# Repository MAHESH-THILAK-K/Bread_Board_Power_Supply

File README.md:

# Bread Board Power Supply

**Board Render**

A compact and easy-to-use breadboard power supply PCB designed to deliver stable, regulated DC power for electronics prototyping. This board plugs directly into standard solderless breadboards and provides clean **5V and/or 3.3V outputs**, making it ideal for students, hobbyists, and embedded system developers.

The design focuses on simplicity, reliability, and beginner-friendly usage for powering microcontrollers, sensors, and logic circuits during development and testing.

---

## 📌 Key Features

### Power Regulation

* Regulated **5V and/or 3.3V DC output**
* Linear voltage regulators for low-noise operation
* Suitable for low-power electronic circuits

### Input Power

* DC input via connector
* Input filtering for stable voltage supply
* Reverse polarity and basic protection (as per schematic)

### Breadboard Compatibility

* Designed to plug directly into breadboard power rails
* Eliminates external power wiring
* Compact footprint for easy placement

### User Indicators

* Power indication LED
* Optional voltage selection (based on design)

---

## 📂 Repository Structure

```
Bread-Board-Power-Supply/
│
├── README.md                # Project documentation
├── LICENSE                  # Open-source license
├── Hardware/
│   ├── Schematic/           # KiCad schematic files (.kicad_sch)
│   ├── PCB/                 # KiCad PCB layout files (.kicad_pcb)
│   └── Gerber/              # Gerber files for manufacturing
├── 3DModels/                # STEP / 3D models (optional)
└── Images/                  # Board renders, photos, diagrams
```

---

## 🛠️ Hardware Overview

### Voltage Regulation

* Linear voltage regulators for 5V / 3.3V output
* Decoupling and filtering capacitors for noise reduction
* Stable output suitable for MCUs and sensors

### Power Distribution

* Direct connection to breadboard power rails
* Even voltage distribution across rails
* Designed for safe current levels

### Indicators & Controls

* Power LED for visual confirmation
* Simple, minimal component design

---

## 🚀 Usage Instructions

1. Insert the PCB into the breadboard power rails.
2. Connect a suitable DC power source.
3. Verify output voltage using a multimeter.
4. Power your breadboard circuits directly from the rails.

No additional wiring or setup is required.

---

## 📄 Manufacturing

The `Hardware/Gerber/` folder includes:

* Top and Bottom copper layers
* Solder mask layers
* Silkscreen layers
* Drill files
* Board outline

These files are ready for fabrication with PCB manufacturers such as **PCBWay**, **JLCPCB**, or **OSH Park**.

---

## 📸 Images & Diagrams

Board renders, PCB layout screenshots, and usage diagrams are available in the:

```
Images/
```

---

## 📜 License

This project is released as **open-source**.
You may choose a suitable license such as:

* CERN-OHL-P-2.0 (recommended for hardware)
* MIT License

---

## 🙌 Contributions

Contributions, improvements, and documentation updates are welcome.
Feel free to open issues or submit pull requests.

---

## 📧 Contact

For questions, suggestions, or collaboration ideas, please open an issue in this repository.

---

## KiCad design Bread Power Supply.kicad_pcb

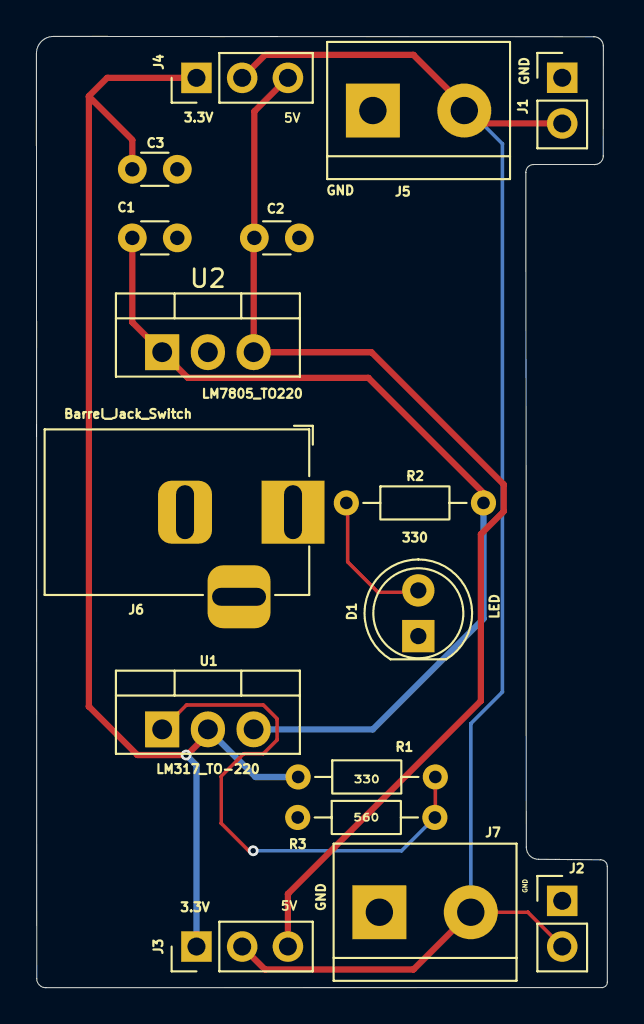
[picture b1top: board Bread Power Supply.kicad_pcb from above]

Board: 2 copper layers, 31.7 x 52.8 mm, 16 parts (0 on the bottom side), 7 nets.

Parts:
C1: 10u; C_Disc_D3.0mm_W1.6mm_P2.50mm
C2: 0.1u; C_Disc_D3.0mm_W1.6mm_P2.50mm
C3: 1u; C_Disc_D3.0mm_W1.6mm_P2.50mm
D1: LED; LED_D5.0mm
J1, J2: Conn_01x02_Pin; PinHeader_1x02_P2.54mm_Vertical
J3, J4: Conn_01x03_Pin; PinHeader_1x03_P2.54mm_Vertical
J5, J7: Screw_Terminal_01x02; TerminalBlock_bornier-2_P5.08mm
J6: Barrel_Jack_Switch; BarrelJack_Horizontal
R1, R2: 330; R_Axial_DIN0204_L3.6mm_D1.6mm_P7.62mm_Horizontal
R3: 560; R_Axial_DIN0204_L3.6mm_D1.6mm_P7.62mm_Horizontal
U1: LM317_TO-220; TO-220-3_Vertical
U2: LM7805_TO220; TO-220-3_Vertical

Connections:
/3.3V: C3.1, J3.1, J4.1, R1.1, U1.2 (VO)
/5V: C2.1, J3.3, J4.3, U2.3 (VO)
/12V: C1.1, R2.2, U1.3 (VI), U2.1 (VI)
/PWR_output: J1.2, J2.2, J3.2, J4.2, J5.2, J7.2
GND: C1.2, C2.2, C3.2, D1.1 (K), J1.1, J2.1, J5.1, J6.2, J6.3, J7.1, R3.1, U2.2 (GND)
unnamed: D1.2 (A), R2.1
unnamed: R1.2, R3.2, U1.1 (ADJ)
